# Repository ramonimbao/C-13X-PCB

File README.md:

# C-13X-PCB

## Features

- ATmega32A
- ai03 daughterboard compatible
- Solder and Kailh hotswap compatible

## How to order

1. JLCPCB.com
2. Upload the gerber zip file from the `Gerbers` directory.
3. Select SMT assembly as an option.
4. Select the bottom side to assemble.
5. Upload the BOM and CPL files from the `JLCPCB` directory.
6. Place your order.
7. ???
8. Profit!

## After ordering

Once you've received the boards, you will have to flash a bootloader on it before being able to flash any QMK firmware on it.

Instructions for that can be found using [here](https://github.com/coseyfannitutti/discipline/blob/master/doc/bootloader/README.md).

## Flashing QMK firmware on it

TBD because I've yet to order boards for myself

## License

This has the same license as the C-13X. See the `LICENSE` file for more details.

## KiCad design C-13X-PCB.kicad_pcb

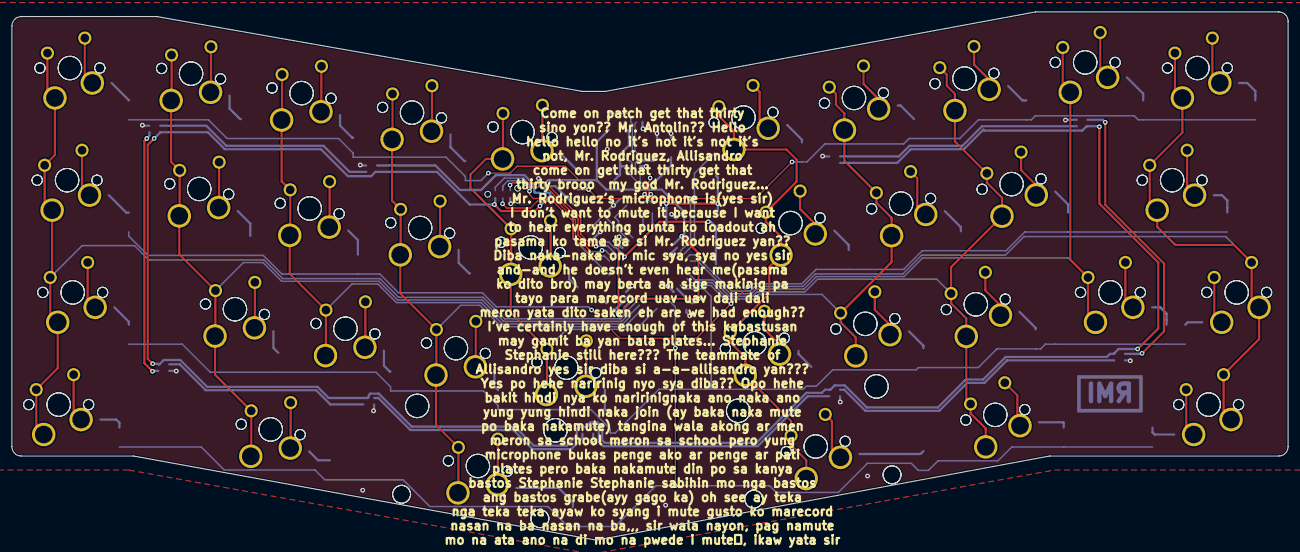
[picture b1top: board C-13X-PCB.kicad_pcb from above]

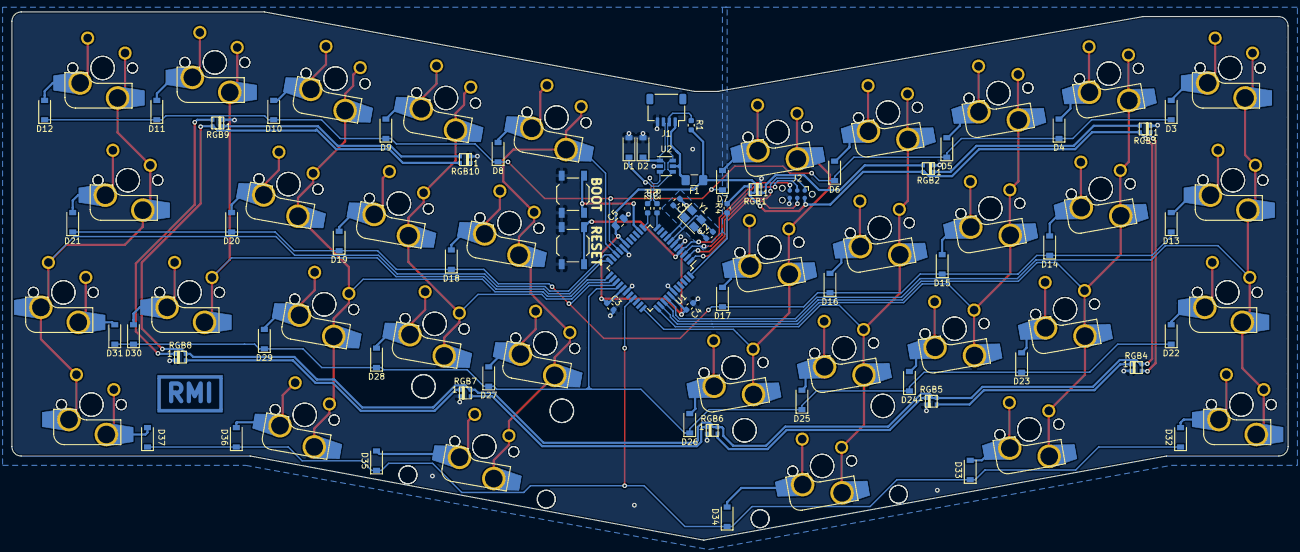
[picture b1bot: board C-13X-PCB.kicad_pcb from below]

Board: 2 copper layers, 216.7 x 89.7 mm, 135 parts (100 on the bottom side), 74 nets.

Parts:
C1, C2: 22pF; C_0603_1608Metric
C3, C4: 100nF; C_0603_1608Metric
C5: 10uF; C_0805_2012Metric
D1, D2: 3.6V; D_SOD-123
D3, D4, D5, D6, D7, D8, D9, D10, D11, D12, D13, D14, D15, D16, D17, D18, D19, D20, D21, D22, D23, D24, D25, D26, D27, D28, D29, D30, D31, D32, D33, D34, D35, D36, D37: 1N4148; D_SOD-123
F1: 500mA; Fuse_1206_3216Metric_Pad1.42x1.75mm_HandSolder
G1: Signature
J1: ai03_Daughterboard_Connector; JST_SH_SM04B-SRSS-TB_1x04-1MP_P1.00mm_Horizontal
J2: AVR-TagConnect; Tag-Connect_TC2030-IDC-NL_2x03_P1.27mm_Vertical
MX1, MX2, MX3, MX4, MX5, MX6, MX7, MX8, MX9, MX10, MX22, MX23, MX24, MX25, MX26, MX27, MX28, MX40, MX41, MX42, MX43, MX44, MX45, MX46, MX48, MX60, MX63: MX-NoLED; MXOnly-1U-NoLED
MX11, MX12, MX13, MX14, MX15, MX16, MX17, MX18, MX19, MX20, MX31, MX32, MX33, MX34, MX35, MX36, MX37, MX50, MX51, MX52, MX53, MX54, MX55, MX56, MX58, MX66, MX69: MX-NoLED; MXOnly-1U-Hotswap-NoLED
MX21, MX47: MX-NoLED; MXOnly-1.25U-NoLED
MX29, MX39: MX-NoLED; MXOnly-1.75U-NoLED
MX30, MX57: MX-NoLED; MXOnly-1.25U-Hotswap-NoLED
MX38, MX49: MX-NoLED; MXOnly-1.75U-Hotswap-NoLED
MX59, MX64: MX-NoLED; MXOnly-1.5U-NoLED
MX61: MX-NoLED; MXOnly-2.75U-ReversedStabilizers-NoLED
MX62: MX-NoLED; MXOnly-2.25U-ReversedStabilizers-NoLED
MX65, MX70: MX-NoLED; MXOnly-1.5U-Hotswap-NoLED
MX67: MX-NoLED; MXOnly-2.75U-Hotswap-NoLED
MX68: MX-NoLED; MXOnly-2.25U-Hotswap-NoLED
R1: 1.5k; R_0603_1608Metric
R2, R3: 75; R_0603_1608Metric
R4: 470; R_0603_1608Metric
RGB1, RGB2, RGB3, RGB4, RGB5, RGB6, RGB7, RGB8, RGB9, RGB10: WS2812B-2020
SW1, SW2: SW_Push; SW_SPST_TL3342
U1: ATmega32A-AU; TQFP-44_10x10mm_P0.8mm
U2: SRV05-4; SOT-23-6
Y1: Crystal_GND24_Small; Crystal_SMD_3225-4Pin_3.2x2.5mm

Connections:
+5V: C3.1, C4.1, C5.1, F1.1, J2.2, R1.2, RGB1.4, RGB2.4, RGB3.4, RGB4.4, RGB5.4, RGB6.4, RGB7.4, RGB8.4, RGB9.4, RGB10.4, U1.5, U1.17, U1.27, U1.38
/A0: MX1.1, MX11.2, MX21.1, MX30.2, MX39.1, MX49.2, MX59.1, MX65.2, U1.37
/A1: MX2.1, MX12.2, MX22.1, MX31.2, MX40.1, MX50.2, MX60.1, MX66.2, U1.36
/A2: MX3.1, MX13.2, MX23.1, MX32.2, MX41.1, MX51.2, U1.35
/A3: MX4.1, MX14.2, MX24.1, MX33.2, MX42.1, MX52.2, MX61.1, MX67.2, U1.34
/A4: MX5.1, MX15.2, MX25.1, MX34.2, MX43.1, MX53.2, U1.33
/A7: D32.1, D33.1, D34.1, D35.1, D36.1, D37.1, U1.30
/C0: D3.1, D4.1, D5.1, D6.1, D7.1, D8.1, D9.1, D10.1, D11.1, D12.1, U1.19
/C1: MX6.1, MX16.2, MX26.1, MX35.2, MX44.1, MX54.2, MX62.1, MX68.2, U1.20
/C2: MX10.1, MX20.2, MX29.1, MX38.2, MX48.2, MX58.1, MX64.2, MX70.1, U1.21
/C3: MX9.1, MX19.2, MX47.1, MX57.2, U1.22
/C4: MX8.1, MX18.2, MX28.1, MX37.2, MX46.1, MX56.2, MX63.1, MX69.2, U1.23
/C5: MX7.1, MX17.2, MX27.1, MX36.2, MX45.1, MX55.2, U1.24
/C6: D13.1, D14.1, D15.1, D16.1, D17.1, D18.1, D19.1, D20.1, D21.1, U1.25
/C7: D22.1, D23.1, D24.1, D25.1, D26.1, D27.1, D28.1, D29.1, D30.1, D31.1, U1.26
/DBUS+: D2.1, J1.3, R3.1, U2.1, U2.3
/DBUS-: D1.1, J1.2, R1.1, R2.2, U2.4, U2.6
/Underglow/RGB: R4.2, RGB1.3
/XTAL+: C2.2, U1.7, Y1.3
/XTAL-: C1.2, U1.8, Y1.1
BOOT: SW2.2, U1.13
D+: R3.2, U1.11
D-: R2.1, U1.12
GND: C1.1, C2.1, C3.2, C4.2, C5.2, D1.2, D2.2, J1.4, J2.6, RGB1.2, RGB2.2, RGB3.2, RGB4.2, RGB5.2, RGB6.2, RGB7.2, RGB8.2, RGB9.2, RGB10.2, SW1.1, SW2.1, U1.6, U1.18, U1.28, U1.39, U2.2, Y1.2, Y1.4
MISO: J2.1, U1.2
MOSI: J2.4, U1.1
NRST: J2.5, SW1.2, U1.4
unnamed: D3.2, MX1.2, MX11.1
unnamed: D4.2, MX2.2, MX12.1
unnamed: D5.2, MX3.2, MX13.1
unnamed: D6.2, MX4.2, MX14.1
unnamed: D7.2, MX5.2, MX15.1
unnamed: D8.2, MX6.2, MX16.1
unnamed: D9.2, MX7.2, MX17.1
unnamed: D10.2, MX8.2, MX18.1
unnamed: D11.2, MX9.2, MX19.1
unnamed: D12.2, MX10.2, MX20.1
unnamed: D13.2, MX21.2, MX30.1
unnamed: D14.2, MX22.2, MX31.1
unnamed: D15.2, MX23.2, MX32.1
unnamed: D16.2, MX24.2, MX33.1
unnamed: D17.2, MX25.2, MX34.1
unnamed: D18.2, MX26.2, MX35.1
unnamed: D19.2, MX27.2, MX36.1
unnamed: D20.2, MX28.2, MX37.1
unnamed: D21.2, MX29.2, MX38.1
unnamed: D22.2, MX39.2, MX49.1
unnamed: D23.2, MX40.2, MX50.1
unnamed: D24.2, MX41.2, MX51.1
unnamed: D25.2, MX42.2, MX52.1
unnamed: D26.2, MX43.2, MX53.1
unnamed: D27.2, MX44.2, MX54.1
unnamed: D28.2, MX45.2, MX55.1
unnamed: D29.2, MX46.2, MX56.1
unnamed: D30.2, MX47.2, MX57.1
unnamed: D31.2, MX48.1, MX58.2
unnamed: D32.2, MX59.2, MX65.1
unnamed: D33.2, MX60.2, MX66.1
unnamed: D34.2, MX61.2, MX67.1
unnamed: D35.2, MX62.2, MX68.1
unnamed: D36.2, MX63.2, MX69.1
unnamed: D37.2, MX64.1, MX70.2
unnamed: RGB1.1, RGB2.3
unnamed: RGB2.1, RGB3.3
unnamed: RGB3.1, RGB4.3
unnamed: RGB4.1, RGB5.3
unnamed: RGB5.1, RGB6.3
unnamed: RGB6.1, RGB7.3
unnamed: RGB7.1, RGB8.3
unnamed: RGB8.1, RGB9.3
unnamed: RGB9.1, RGB10.3
RGB: R4.1, U1.44
SCLK: J2.3, U1.3
VBUS: F1.2, J1.1, U2.5

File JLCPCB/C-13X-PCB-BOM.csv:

Comment,Designator,Footprint,LCSC
22pF,"C1,C2",Capacitor_SMD:C_0603_1608Metric,C1653
100nF,"C3,C4",Capacitor_SMD:C_0603_1608Metric,C14663
10uF,C5,Capacitor_SMD:C_0805_2012Metric,C15850
3.6V,"D1,D2",Diode_SMD:D_SOD-123,C2891771
1N4148W,"D3,D4,D5,D6,D7,D8,D9,D10,D11,D12,D13,D14,D15,D16,D17,D18,D19,D20,D21,D22,D23,D24,D25,D26,D27,D28,D29,D30,D31,D32,D33,D34,D35,D36,D37",Diode_SMD:D_SOD-123,C81598
500mA,F1,Fuse:Fuse_1206_3216Metric_Pad1.42x1.75mm_HandSolder,C69688
ai03_Daughterboard_Connector,J1,Connector_JST:JST_SH_SM04B-SRSS-TB_1x04-1MP_P1.00mm_Horizontal,C160404
MX-NoLED,"MX11,MX12,MX13,MX14,MX15,MX16,MX17,MX18,MX19,MX20,MX31,MX32,MX33,MX34,MX35,MX36,MX37,MX50,MX51,MX52,MX53,MX54,MX55,MX56,MX58,MX66,MX69",MX_HS:MXOnly-1U-Hotswap-NoLED,C5156480
MX-NoLED,"MX30,MX57",MX_HS:MXOnly-1.25U-Hotswap-NoLED,C5156480
MX-NoLED,"MX38,MX49",MX_HS:MXOnly-1.75U-Hotswap-NoLED,C5156480
MX-NoLED,"MX65,MX70",MX_HS:MXOnly-1.5U-Hotswap-NoLED,C5156480
MX-NoLED,MX67,MX_HS:MXOnly-2.75U-Hotswap-NoLED,C5156480
MX-NoLED,MX68,MX_HS:MXOnly-2.25U-Hotswap-NoLED,C5156480
1.5k,R1,Resistor_SMD:R_0603_1608Metric,C22843
75,"R2,R3",Resistor_SMD:R_0603_1608Metric,C4275
470,R4,Resistor_SMD:R_0603_1608Metric,C23179
WS2812B-2020,"RGB1,RGB2,RGB3,RGB4,RGB5,RGB6,RGB7,RGB8,RGB9,RGB10",random-keyboard-parts:WS2812B-2020,C965555
SW_Push,"SW1,SW2",Button_Switch_SMD:SW_SPST_TL3342,C318884
ATmega32A-AU,U1,Package_QFP:TQFP-44_10x10mm_P0.8mm,C5659
SRV05-4,U2,Package_TO_SOT_SMD:SOT-23-6,C85364
Crystal_GND24_Small,Y1,Crystal:Crystal_SMD_3225-4Pin_3.2x2.5mm,C13738

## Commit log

2023-02-22 Add LCSC part numbers in BOM, fix RGB
